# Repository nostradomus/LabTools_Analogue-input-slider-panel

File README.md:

# **LabTools** : Analogue input slider panel

## What

This slider panel is part of a homemade toolset of modules to simplify the r&d phase of my µ-controller projects. It consists of four [linear slider potentiometers](pdf-files/Bourns-slider-potentiometer-datasheet.pdf), which are connected as [voltage dividers](https://en.wikipedia.org/wiki/Voltage_divider). Built with the component values as stated in the bill-of-materials, the panel is optimized for 0 to 5V ADC's. Thanks to its universal layout, the module can easily be adapted for other voltage ranges, by changing the resistor values.

## Why

Whilst playing around with µ-controllers and their peripherals, I got often confronted with the need for analogue values for various reasons.
 - When designing a [ternary clock](https://github.com/nostradomus/Base3-clock) I had a need to mix my own cool colors to display with the RGB LED's in this project. The slider panel was just what I needed, as I could easily simulate the three color channels red, green and blue, plus the brightness on the fourth slider.
 - Next on a rainy Sunday, we decided to have some fun, and build our version of the [cool O++O robot](https://github.com/OttoDIY/OttoDIY). This cute little guy is running, or rather, dancing on four servos. In a project with *constrainted* movements, it is interesting to test the mechanical limits of your rotations before breaking any of your nice 3D-printed parts. YAGA ! **Yet another great application** for the slider panel.
 - When working with servos, not only the angular limits are important, but for several applications also the center point of the circular movement. This came in handy for a robot arm project based on radial coordinates.  
 - A completely different, but obvious example, was application testing. For practical reasons, most of the time, it is preferable to replace physical sensors by **controlled** test values. In pure programming these usually originate from test units. With this type of methodology however, it is utmost impossible to do exhaustive testing. Especially when combining multiple analogue values. For that matter, as an extra test, the slider panel has proven to be very handy.  
 - And their will probably be dozens of other useful applications for this little lab tool...

## How

Simple projects don't need complicated specifications. However once you start, there's always a couple of nice-to-haves you just have to go for.
 - The [slider potentiometers](pdf-files/Bourns-slider-potentiometer-datasheet.pdf) should  
    - have a reasonable travel length for precision
    - have a linear taper
    - have a center detent
    - exist in different resistance values (10kΩ and higher)
    - have a built-in indicator LED
 - The [housing](#mechanical-construction) should have
    - an ID for each slider
    - labels for each pin on the interface connector
 - And the whole thing must be **fancy** :sunglasses: !

## Progress status

 - [x] having a [need](#why)
 - [x] define the [functional specifications](#how)
 - [x] design the final [electronics](#electronics)
 - [x] build a proof-of-concept for the final [electronics](#electronics)
 - [x] write [code for the µ-controller](#µ-controller-code) respecting best-practices
 - [x] design and build a [state-of-the-art housing](#mechanical-construction)
 - [x] validate the [application examples](#µ-controller-code) with in-line documentation

## Technical details

### The voltage divider, the ADC and the mapping function

The whole setup of this mini-project is based on three crucial denominators, two in the electronics, and one in software.

The first part of the magic happens inside the potentiometer which is connected as a [voltage divider](https://en.wikipedia.org/wiki/Voltage_divider). Some current will flow from +5V to ground through the 10kΩ resistor. The third wire (or center tap) of the potentiometer gives us a variable connection on that 10kΩ range, which actually splits it into two resistors (which add up to be the full resistance). In such a passive resistive-only circuit, the center tap will output a voltage which is proportional to the total potential, the same way as the fractions of the two resistors are to the total resistance. Next, as the [chosen slider potentiometer](pdf-files/Bourns-slider-potentiometer-datasheet.pdf) is of good linear quality, the output will even be equally proportional to the slider's position on the total slider travel length.  

The second step is where the µ-controller will convert this (physical) voltage in a software readable value. This is called an [ADC, or analogue-to-digital converter](https://en.wikipedia.org/wiki/Analog-to-digital_converter). They exist in numerous varieties of architectures, conversion types, speeds, precision... For the below examples, I will use the [ATmega328p](pdf-files/datasheet-ATmega328P.pdf)'s built-in ADC's. They are marked as A0, A1, A2... Being of 10-bit precision, the conversion of the 0 to 5V voltage will give a value between 0 and 1023. More details on this specific ADC can be found from [page 237 to 248 in the µ-controller's datasheet](pdf-files/datasheet-ATmega328P.pdf).

The last trick to be done is converting the 0 to 1023 value to the range for our application. In below examples, colors and PWM outputs need to be set. All of these need byte-values. For PWM 0 to 255, and for RGB-colors (0..255,0..255,0..255). You could of course write some simple equations to apply the rule of three. However the C-language in the [Arduino IDE](https://www.arduino.cc/en/Main/Software) is having a very handy function for that, called [mapping](https://www.arduino.cc/en/reference/map).
```C
recalculated_value = map(value, fromLow, fromHigh, toLow, toHigh);
// example : x = map(511,0,1023,0,255)
//           -> gives x = 127
```
### The Electronics

#### The Schematic

The electronics setup is straightforward and easy to understand. Four [variable resistors P1 to P4 (linear sliders), or potentiometers](pdf-files/Bourns-slider-potentiometer-datasheet.pdf) are connected between +5V and ground. Depending on the position, the slider-pin will output a voltage between 0 and 5V. This can be directly connected to your µ-controller's analogue input, or ADC. The (optional) LED's in the slider button have been fit with 2,7kΩ resistors (R1 to R4), to limit the current flowing through, and to not make you blind :sunglasses:. For connector CON1, a **90° bent** 10x1 pin-header is preferred, for easy access in combination with the laser-cut housing.

#### The PCB

The PCB has been designed single-sided with wide traces for "kitchen-brew" production. The larger pcb size and generous spacing between the [potentiometers](pdf-files/Bourns-slider-potentiometer-datasheet.pdf) is mainly for ergonomical reasons. Be precise when drilling the holes in the pcb, as the quality of the mechanical construction depends on correct positioning of the potentiometers and the four mounting holes.

#### BOM - bill of materials

Part | Value | Package | Description  
---- | ----- | ------- | -----------                                                                      
R1,2,3,4 | 2,7kΩ | 0204/7             | resistor                                            
P1,2,3,4 | 10kΩ  | SLIDER_POT_60_WLED | Bourns slider potentiometer (60mm) with LED
CON1     | 1x10  | 1x10 90°           | 90° bent pin header

#### Connection with a µ-controller board

The board has been designed with a 10-way (90° bent) pin-header for easy connection with standard Dupont lines, typically used for testing during breadboard phase.

:electric_plug:|name |description
---------------|-----|----------------------------------
1              |GND  | ground
2              |LED1 | indicator led on potentiometer 1
3              |P1   | variable output on potentiometer 1
4              |LED2 | indicator led on potentiometer 2
5              |P2   | variable output on potentiometer 2
6              |LED3 | indicator led on potentiometer 3
7              |P3   | variable output on potentiometer 3
8              |LED4 | indicator led on potentiometer 4
9              |P4   | variable output on potentiometer 4
10             |+5V  | 5 volt power Connection

In a minimum setup, pins 1 and 10 (power and ground), and at least one Px output need to be connected. When using an Arduino eco-system, the potentiometer's variable output can be connected directly to any of the µ-controller's analogue inputs which accept 0 to 5V. The *optional* led connections can either be connected directly to the ground (always ON), or to a digital output of the µ-controller (capable of sinking at least 10mA). When building the full project (lasercut plexi included), you will see the connection descriptors engraved in the rear-panel, just above the pin-header.

### µ-Controller code

The demo/test software has been written in the free [Arduino IDE](https://www.arduino.cc/en/Main/Software), or as [sourcecode](https://github.com/arduino/Arduino/).
These examples are using the [servo library](https://www.arduino.cc/en/Reference/Servo), which is included in the Arduino IDE software, and [Adafruit's Neopixel library](https://github.com/adafruit/Adafruit_NeoPixel). All sketches can be found in the [source-folder](source/).

#### Application example 1 : Robot servo calibration

A basic [servo calibration application](source/robotarm-servo-calibration.ino) is available in the [source-folder](source/). The Arduino sketch contains extensive comments on how to connect and run the application. The basic idea is to first find the clockwise :leftwards_arrow_with_hook: and counterclockwise :arrow_right_hook: limits of a servo inside your mechanical construction. Secondly, in many construction you might also be interested in the mid-point between these to limits. And, this is not necessarily CW :leftwards_arrow_with_hook: plus CCW :arrow_right_hook: divided by two ! Next, in the serial monitor, you can read the settings to be used in your future application. By using the CW :leftwards_arrow_with_hook: and CCW :arrow_right_hook: limits as parameters 4 and 5 in the mapping function, you can easily prevent mechanical overshoot (and damage) while fine-tuning your mechanics. Before connecting your mechanical construction, it would be a good idea to set the slider potentiometers at 50%, and to position your servos about half-way of their possible movement. When starting the application, the serial monitor will provide connection and setup info. Next, the software will slowly move the servos to the position as preset by the potentiometers. Once the sketch reaches the main-loop, things might be more reactive. So, handle with care :collision: :exclamation: When changing the value of a slider, its button LED will remain ON, as long as the servo is moving towards its new angular position.

#### Application example 2 : RGB LED color mixer

A basic [color mixer application](source/RGB-LED-color-mixer.ino) is available in the [source-folder](source/). The Arduino sketch contains extensive comments on how to connect and run the application. The basic idea is to brew your own color by mixing R(ed), G(reen) and B(lue) until you like the result visually. Next, in the serial monitor, you can read the settings to be used in your future application (0..255,0..255,0..255). Slider number 4 will let you play with the overall brightness, and provide feedback in the serial monitor accordingly. When starting the application, the serial monitor will provide connection and setup info, followed by a short LED test.

For those who prefer more fancy feedback, an extended version of the [color mixer application](source/RGB-LED-color-mixer-with-indicators.ino) is also available. This version has code implemented to use the LED's on the slider buttons. When one of the sliders is moved, its button-LED will switch ON. This indicates that the associated value had a change above the preset threshold (configurable value). The LED will remain ON for three seconds (configurable value).

### Mechanical construction

The housing consists of two layers of lasercut and engraved plexi plates. I would suggest to use 3mm of thickness. When using another thickness, pay attention to adapt the length of screws and bolts.

Material :
 - 4 nylon bolts, M3 x 8
 - 8 nylon nuts, M3
 - 8 metal screws, M2 x 4 (optionally with conic head)

The four nylon bolts fit in the four holes of the rear plexi plate. The heads should be down, as they will serve as feet for the module. The rear panel has to be turned, in a way that the connector info (GND-P1-L1-P2...) is readable on the top. Next four nylon bolts are fit on the threading (which points up). These standard bolts are thick enough to serve as spacers for the PCB, which has to be fit on top. The other four nylon bolts will be used to fix the PCB. The front plate (with 1-2-3-4 on top) is fixed on the metal slider housings with the 8 metal screws. The prototype has been built with standard flat-head screws. The 3mm plexi is however thick enough to be adapted for screws with a conic head (extra milling required).

## Contributors

If you are having any good suggestions, just drop me a line [:email:](http://nostradomus.ddns.net/contactform.html).
If feasible, I'll be happy to implement proposed improvements.
And if you are having lots of time, I'll be happy to share the work with you ;-).

When you create your own version, don't forget to send us some nice pictures of your construction. We'll be happy to publish them in the :confetti_ball:Hall of Fame:confetti_ball:.

## :globe_with_meridians: License

There is no specific license attached to this project for personal use.

If you like it, have fun with it (at your own risk of course :-D), and especially, be creative.

Oh, and when using anything from this repository, it is highly appreciated if you mention its origin.

If you would like to use any of my work (or the whole project) for commercial use, just [contact me :email:](http://nostradomus.ddns.net/contactform.html), so we can agree on an appropriate license, which best fits your business.

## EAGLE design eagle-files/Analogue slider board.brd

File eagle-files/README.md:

This folder will contain all files required to open the project in the EAGLE PCB software [(download here)](http://www.autodesk.com/products/eagle/free-download) : 

 - .epf : the project file as main entry point (is connected with the description file)
 - .sch : schematic file
 - .brd : pcb layout file
 
 These files should (grouped in a folder) either be copied in Eagle's project directory (see below image of the settings window). The Eagle directory settings also accept multiple paths. The Eagle syntax requires columns as path separators.

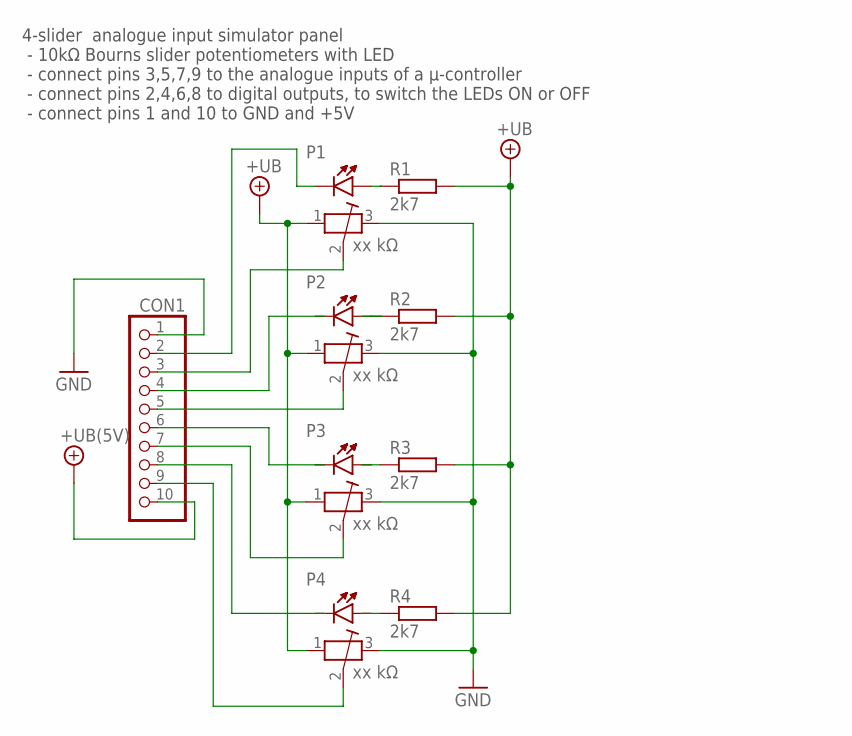
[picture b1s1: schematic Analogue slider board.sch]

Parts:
CON1: PINHD-1X10; 1X10
P1, P2, P3, P4: 10kΩ; SLIDER_POT_60_WLED
R1, R2, R3, R4: 2k7; 0204/7

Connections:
+UB: CON1.10, P1.1, P2.1, P3.1, P4.1, R1.2, R2.2, R3.2, R4.2
GND: CON1.1, P1.3, P2.3, P3.3, P4.3
unnamed: P1.B (B(+)), R1.1
unnamed: P2.B (B(+)), R2.1
unnamed: P3.B (B(+)), R3.1
unnamed: P4.B (B(+)), R4.1
unnamed: CON1.3, P1.2
unnamed: CON1.5, P2.2
unnamed: CON1.7, P3.2
unnamed: CON1.9, P4.2
unnamed: CON1.8, P4.E (E(-))
unnamed: CON1.6, P3.E (E(-))
unnamed: CON1.4, P2.E (E(-))
unnamed: CON1.2, P1.E (E(-))

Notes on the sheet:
4-slider analogue input simulator panel - 10kΩ Bourns slider potentiometers with LED - connect pins 3,5,7,9 to the analogue inputs of a µ-controller - connect pins 2,4,6,8 to digital outputs, to switch the LEDs ON or OFF - connect pins 1 and 10 to GND and +5V

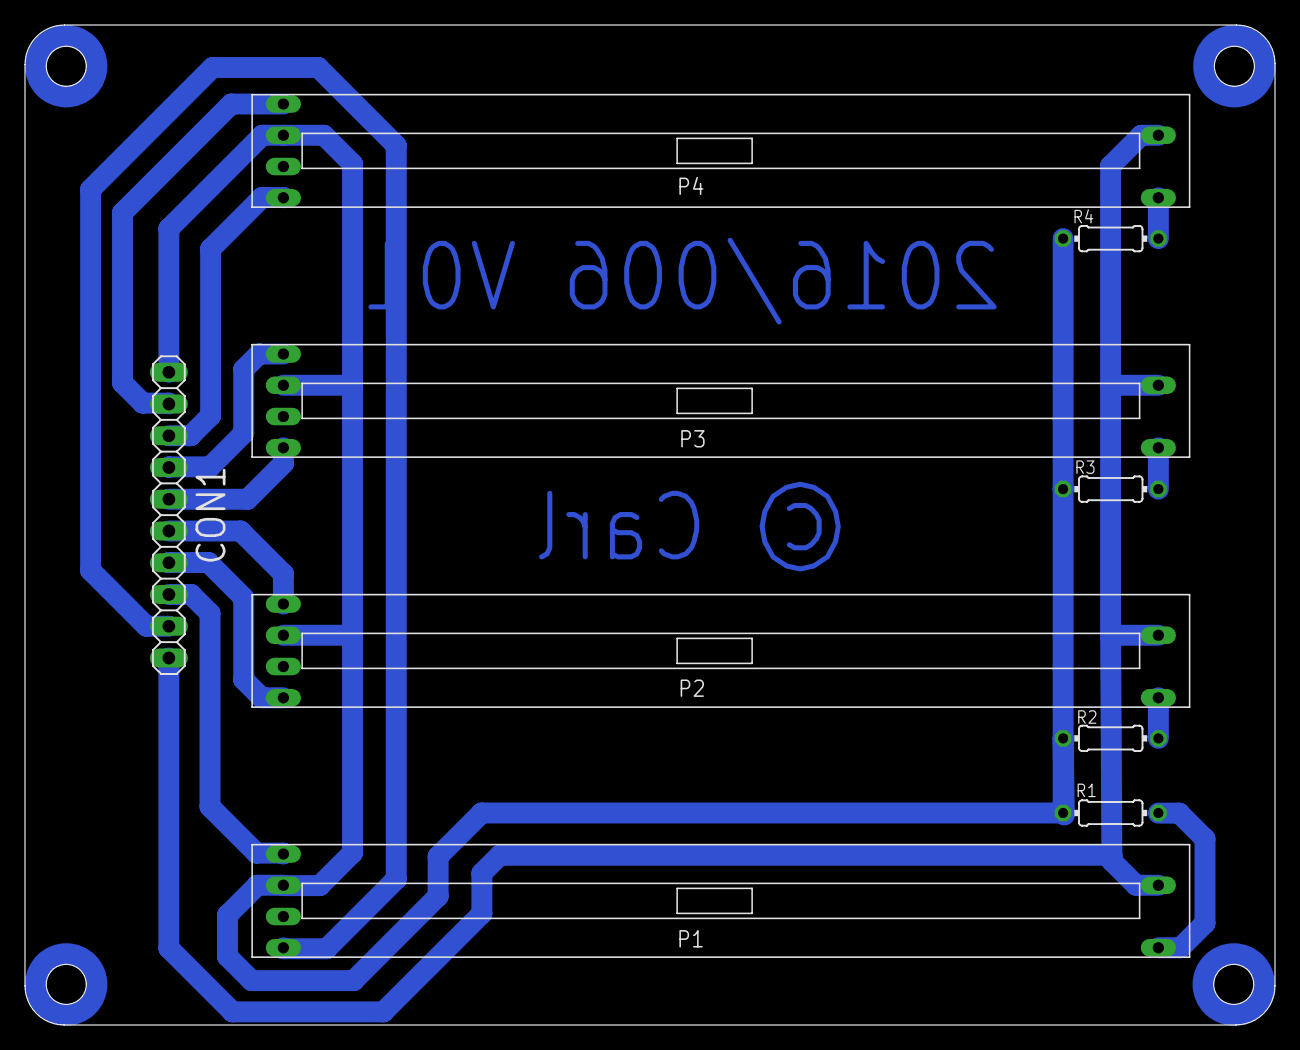
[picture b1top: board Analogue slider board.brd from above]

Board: 2 copper layers, 100.0 x 80.0 mm, 9 parts (0 on the bottom side), 14 nets.

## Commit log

2017-06-01 Potentiometer jitter masking mechanism updated
2017-06-01 Alternative version for color calibration with button LED indicators uploaded

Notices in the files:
eagle-files/Analogue slider board.brd:
© Carl
